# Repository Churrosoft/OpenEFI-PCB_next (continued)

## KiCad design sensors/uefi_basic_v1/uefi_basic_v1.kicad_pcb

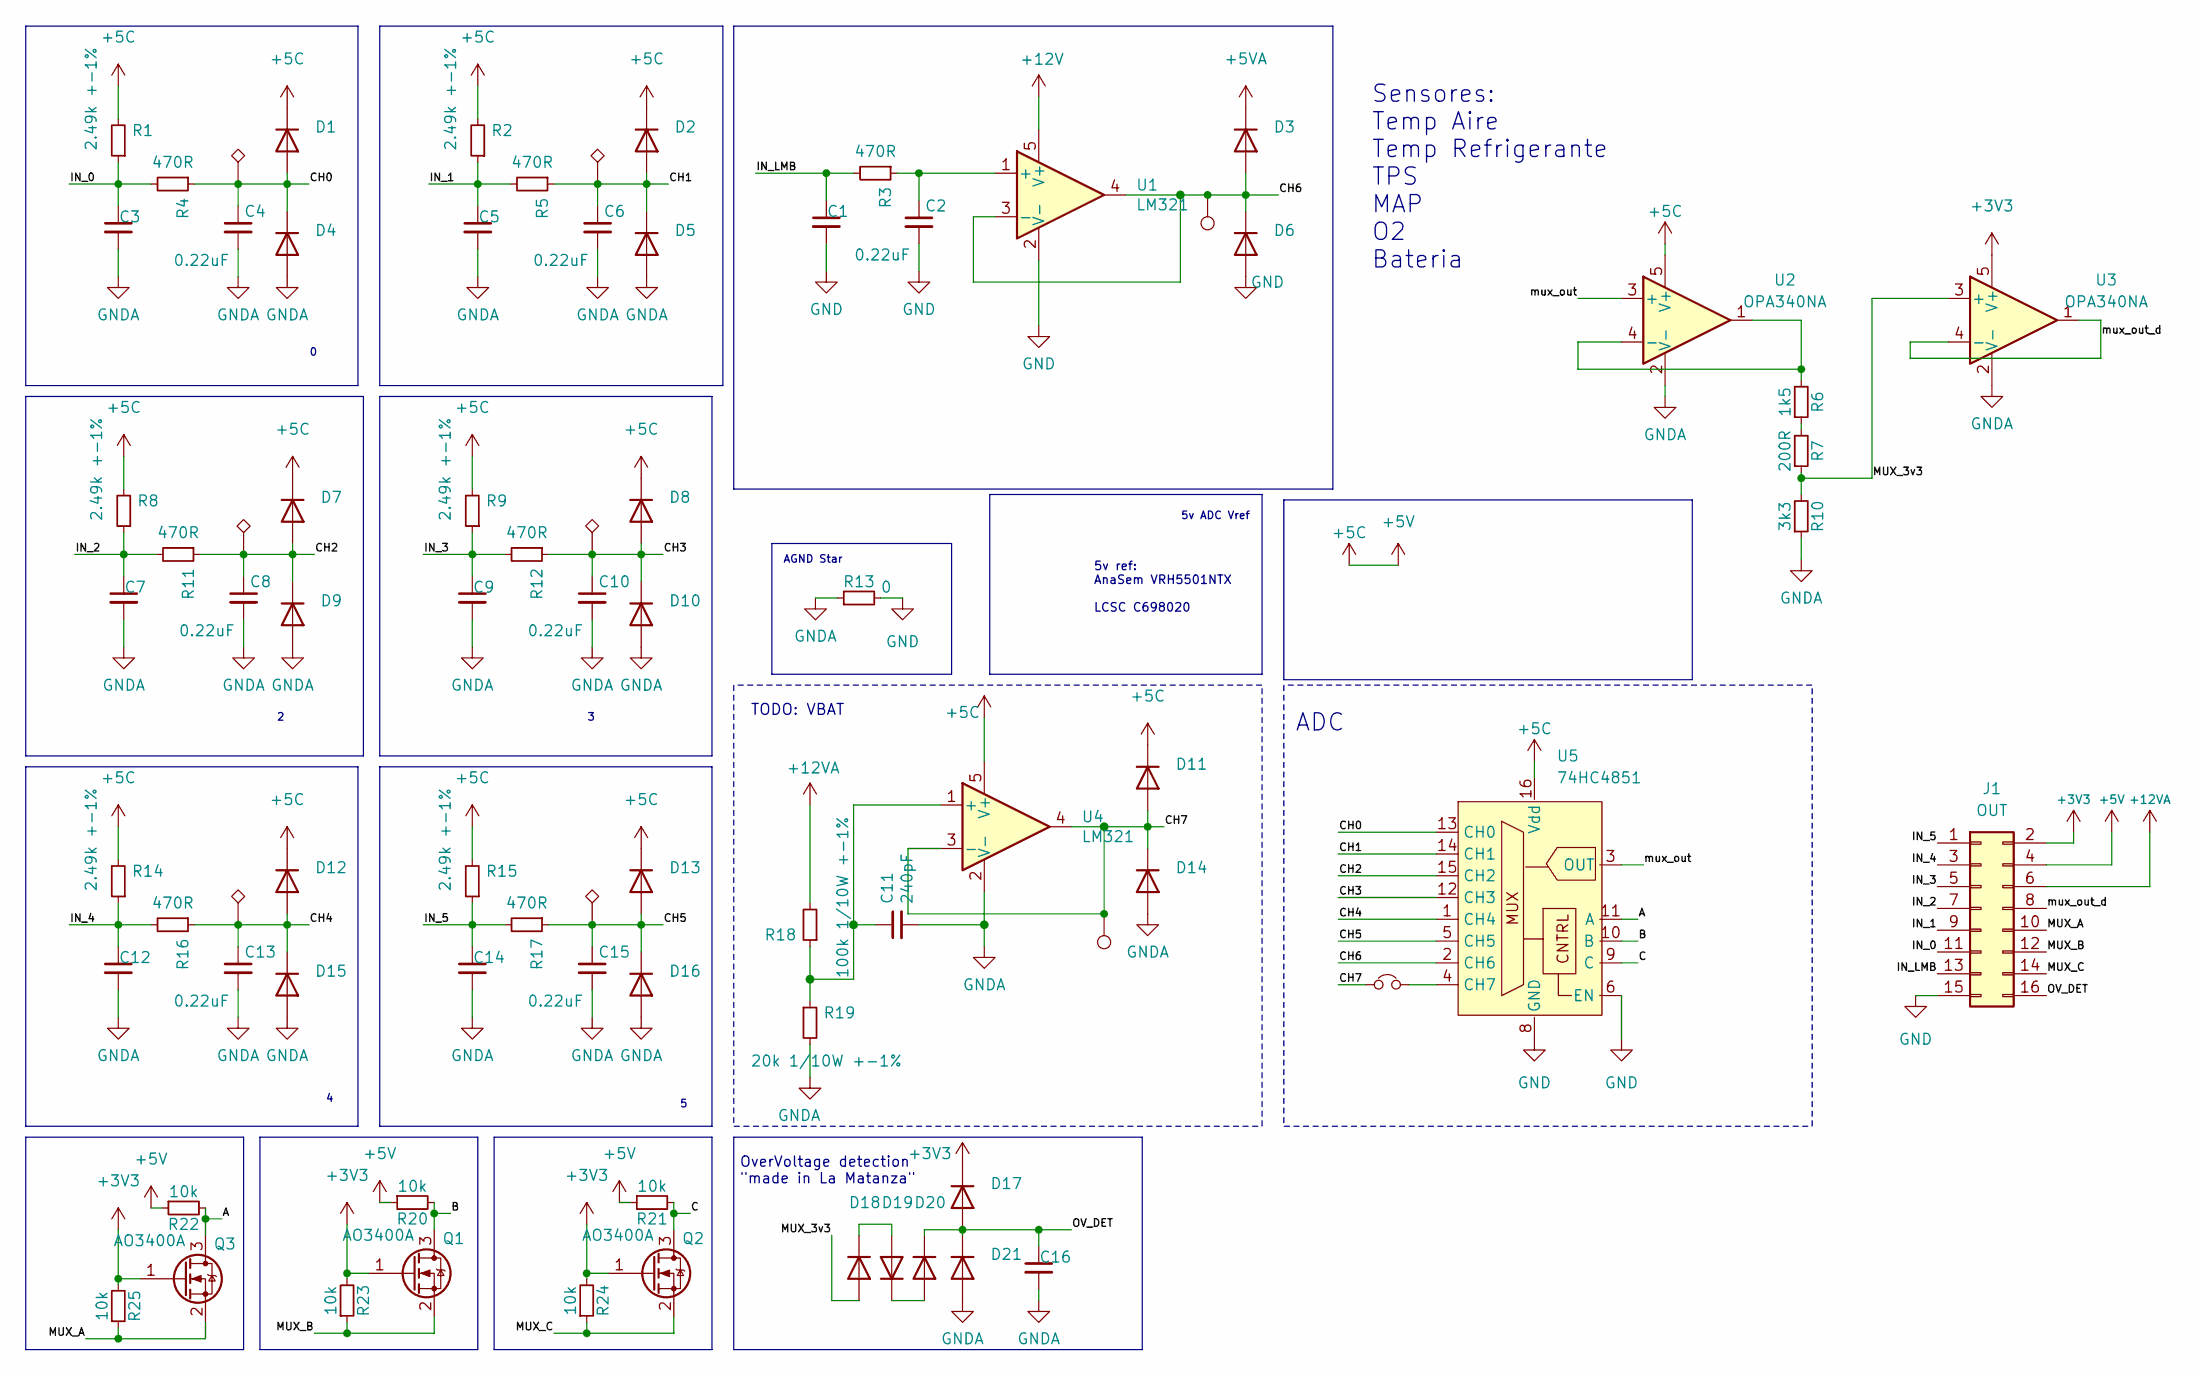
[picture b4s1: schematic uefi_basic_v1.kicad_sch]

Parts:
C1, C3, C5, C7, C9, C12, C14, C16: 100nF; C_0805_2012Metric; LCSC C49678
C2, C4, C6, C8, C10, C13, C15: 0.22uF; C_0603_1608Metric
C11: 240pF; C_0603_1608Metric; LCSC C185593
D1, D2, D3, D4, D5, D6, D7, D8, D9, D10, D11, D12, D13, D14, D15, D16, D17, D18, D19, D20, D21: K26; D_SOD-323; LCSC C2922179
J1: OUT; PinHeader_2x08_P2.54mm_Vertical
JP1: Jumper_NC_Small; SolderJumper-2_P1.3mm_Open_TrianglePad1.0x1.5mm
Q1, Q2, Q3: AO3400A; SOT-23; LCSC C347475
R1, R2, R8, R9, R14, R15: 2.49k +-1%; R_0603_1608Metric
R3, R4, R5, R11, R12, R16, R17: 470R; R_0603_1608Metric
R6: 1k5; R_0603_1608Metric
R7: 200R; R_0603_1608Metric
R10: 3k3; R_0603_1608Metric
R13: 0; R_0603_1608Metric
R18: 100k 1/10W +-1%; R_0603_1608Metric; LCSC C217840
R19: 20k 1/10W +-1%; R_0603_1608Metric
R20, R21, R22, R23, R24, R25: 10k; R_0603_1608Metric
TP1, TP2, TP4, TP5, TP7, TP8: TestPoint_Alt; TestPoint_THTPad_1.0x1.0mm_Drill0.5mm
TP3, TP6: TestPoint; TestPoint_Pad_2.0x2.0mm
U1, U4: LM321; SOT-23-5
U2, U3: OPA340NA; SOT-23-5
U5: 74HC4851; SOIC-16_3.9x9.9mm_P1.27mm; LCSC C233468

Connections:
+3V3: D17.1 (K), J1.2, Q1.1 (G), Q2.1 (G), Q3.1 (G), R23.2, R24.2, R25.2, U3.5 (V+)
+5C: D1.1 (K), D2.1 (K), D7.1 (K), D8.1 (K), D11.1 (K), D12.1 (K), D13.1 (K), J1.4, R1.2, R2.2, R8.2, R9.2, R14.2, R15.2, R20.1, R21.1, R22.1, U2.5 (V+), U4.5 (V+), U5.16 (Vdd)
+5VA: D3.1 (K)
+12V: U1.5 (V+)
+12VA: J1.6, R18.2
/A: Q3.3 (D), R22.2, U5.11 (A)
/B: Q1.3 (D), R20.2, U5.10 (B)
/C: Q2.3 (D), R21.2, U5.9 (C)
/CH0: C4.1, D1.2 (A), D4.1 (K), R4.1, TP1.1, U5.13 (CH0)
/CH1: C6.1, D2.2 (A), D5.1 (K), R5.1, TP2.1, U5.14 (CH1)
/CH2: C8.1, D7.2 (A), D9.1 (K), R11.1, TP4.1, U5.15 (CH2)
/CH3: C10.1, D8.2 (A), D10.1 (K), R12.1, TP5.1, U5.12 (CH3)
/CH4: C13.1, D12.2 (A), D15.1 (K), R16.1, TP7.1, U5.1 (CH4)
/CH5: C15.1, D13.2 (A), D16.1 (K), R17.1, TP8.1, U5.5 (CH5)
/CH6: D3.2 (A), D6.1 (K), TP3.1, U1.3 (-), U1.4, U5.2 (CH6)
/CH7: D11.2 (A), D14.1 (K), JP1.1, TP6.1, U4.3 (-), U4.4
/IN_0: C3.1, J1.11, R1.1, R4.2
/IN_1: C5.1, J1.9, R2.1, R5.2
/IN_2: C7.1, J1.7, R8.1, R11.2
/IN_3: C9.1, J1.5, R9.1, R12.2
/IN_4: C12.1, J1.3, R14.1, R16.2
/IN_5: C14.1, J1.1, R15.1, R17.2
/IN_LMB: C1.1, J1.13, R3.2
/MUX_3v3: D18.2 (A), R7.1, R10.2, U3.3 (+)
/MUX_A: J1.10, Q3.2 (S), R25.1
/MUX_B: J1.12, Q1.2 (S), R23.1
/MUX_C: J1.14, Q2.2 (S), R24.1
/OV_DET: C16.1, D17.2 (A), D20.1 (K), D21.1 (K), J1.16
/mux_out: U2.3 (+), U5.3 (OUT)
/mux_out_d: J1.8, U3.1, U3.4 (-)
GND: C1.2, C2.2, D6.2 (A), J1.15, R13.2, U1.2 (V-), U5.6 (EN), U5.8 (GND)
GNDA: C3.2, C4.2, C5.2, C6.2, C7.2, C8.2, C9.2, C10.2, C11.2, C12.2, C13.2, C14.2, C15.2, C16.2, D4.2 (A), D5.2 (A), D9.2 (A), D10.2 (A), D14.2 (A), D15.2 (A), D16.2 (A), D21.2 (A), R10.1, R13.1, R19.2, U2.2 (V-), U3.2 (V-), U4.2 (V-)
unnamed: C2.1, R3.1, U1.1 (+)
unnamed: C11.1, R18.1, R19.1, U4.1 (+)
unnamed: D18.1 (K), D19.2 (A)
unnamed: D19.1 (K), D20.2 (A)
unnamed: JP1.2, U5.4 (CH7)
unnamed: R6.1, R7.2
unnamed: R6.2, U2.1, U2.4 (-)

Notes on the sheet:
OverVoltage detection "made in La Matanza"
Sensores: Temp Aire Temp Refrigerante TPS MAP O2 Bateria
5v ADC Vref
AGND Star
5v ref: AnaSem VRH5501NTX LCSC C698020
ADC
TODO: VBAT

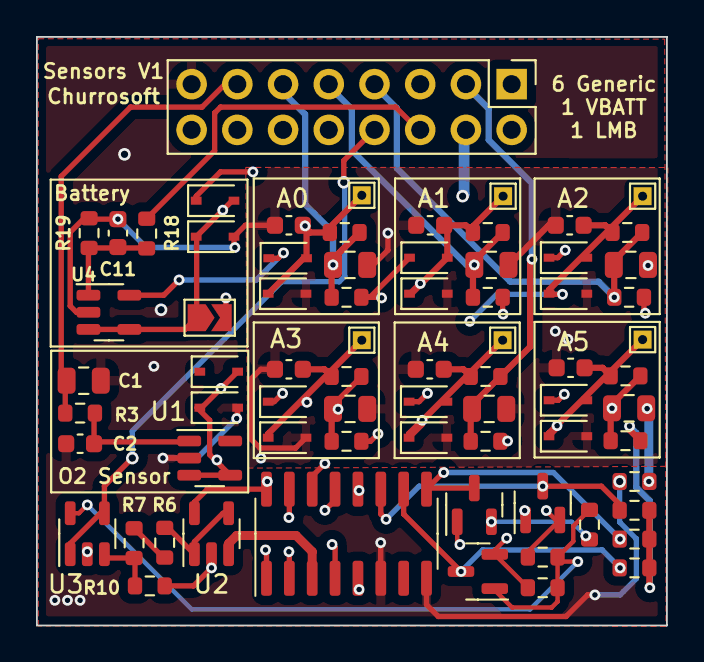
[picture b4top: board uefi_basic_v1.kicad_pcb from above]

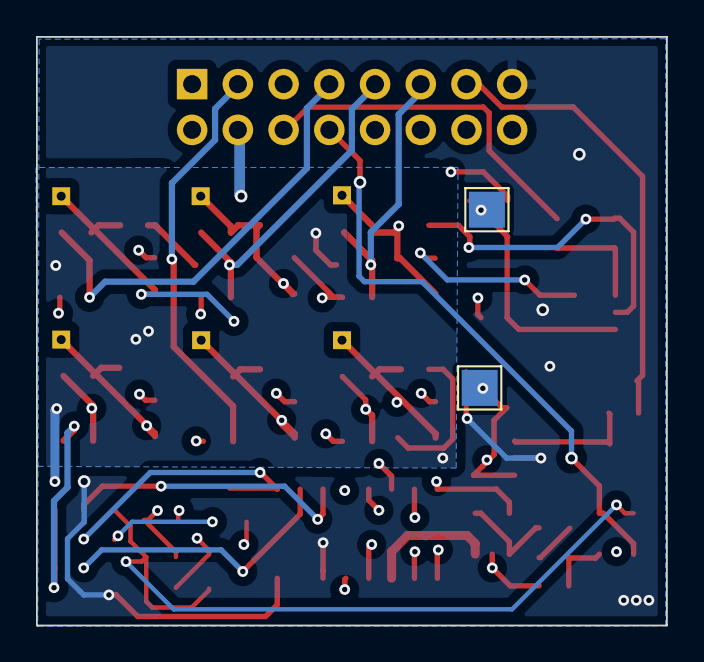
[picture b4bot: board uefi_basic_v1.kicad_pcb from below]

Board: 4 copper layers, 35.0 x 32.7 mm, 74 parts (2 on the bottom side), 34 nets.

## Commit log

2023-01-16 WIP: pmic module
2023-01-18 basic driver v1
2023-01-31 wip uefi mainboard
2023-02-01 wip uefi v4 mainboard
2023-02-02 wip uefi mainboard, led wiring
2023-02-02 uefi v4 mainboard, wip relay
